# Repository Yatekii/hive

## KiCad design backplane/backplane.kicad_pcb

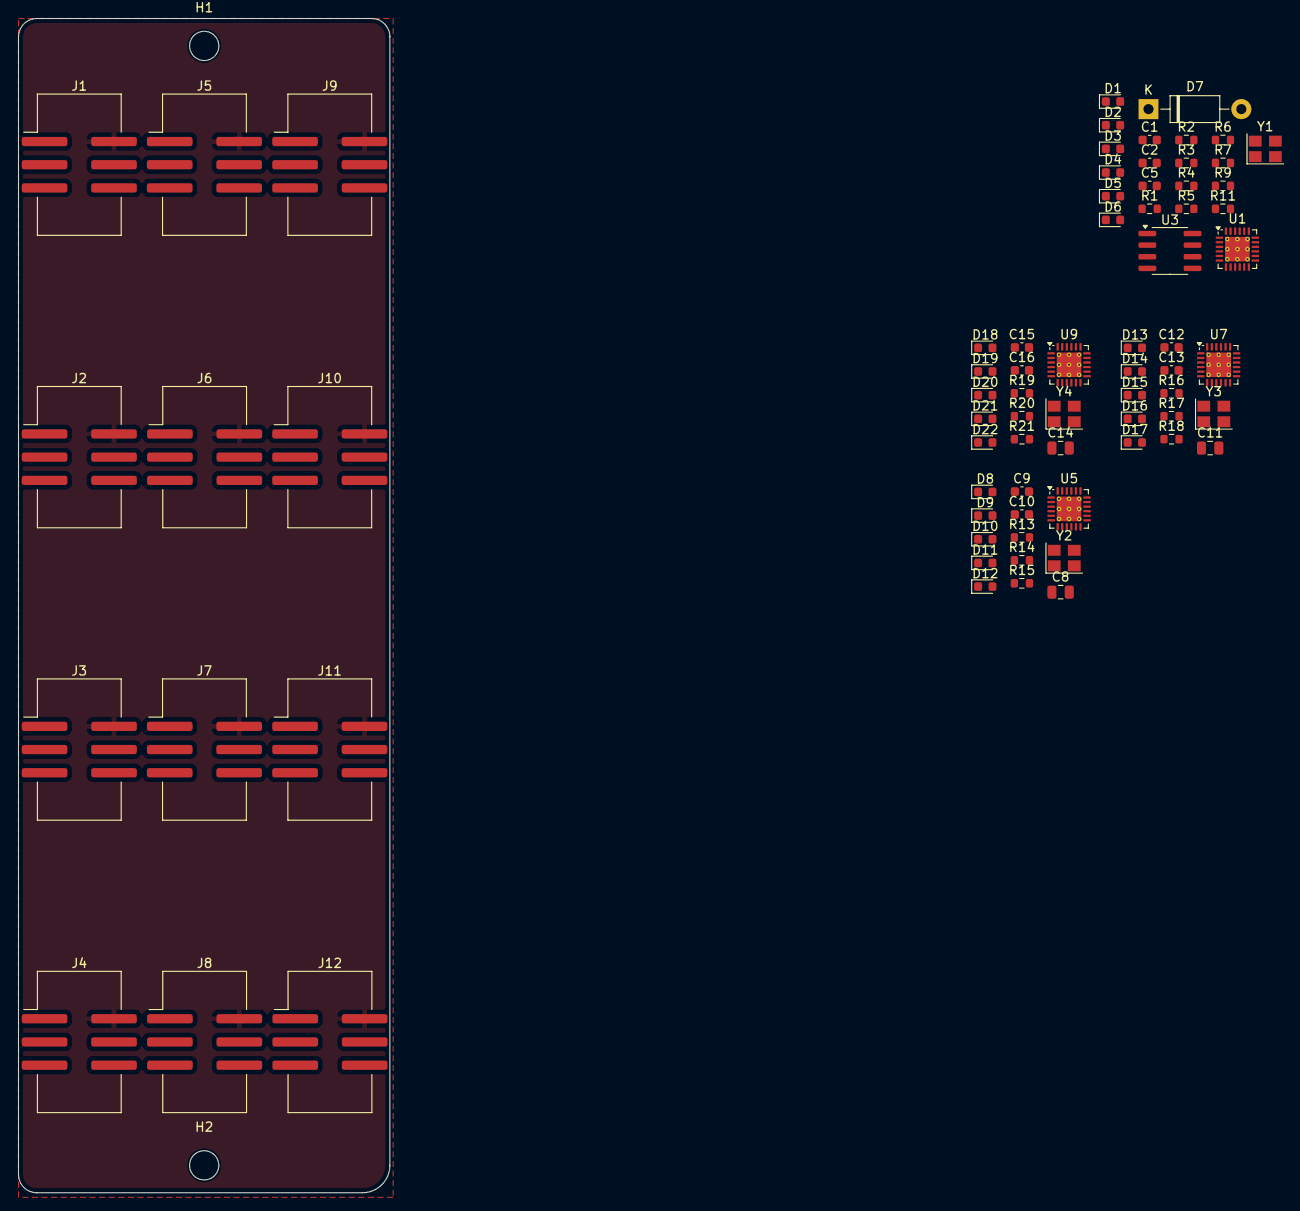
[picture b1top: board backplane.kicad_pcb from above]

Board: 2 copper layers, 40.6 x 128.5 mm, 75 parts (0 on the bottom side), 32 nets, no tracks yet.

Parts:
C1, C2, C5, C9, C10, C12, C13, C15, C16: 10u; C_0603_1608Metric
C8, C11, C14: 22uF; C_0805_2012Metric
D1, D2, D3, D4, D8, D9, D10, D11, D13, D14, D15, D16, D18, D19, D20, D21: GREEN; D_0603_1608Metric
D5, D12, D17, D22: RED; D_0603_1608Metric
D6: WHITE; D_0603_1608Metric
D7: 1N5819; D_DO-41_SOD81_P10.16mm_Horizontal
H1, H2: MountingHole; MountingHole_3.2mm_M3
J1, J2, J3, J4, J5, J6, J7, J8, J9, J10, J11, J12: Conn_02x03_Odd_Even; IDC-Header_2x03_P2.54mm_Vertical_SMD
R1, R2, R13, R14, R16, R17, R19, R20: 220; R_0603_1608Metric
R3, R15, R18, R21: 470; R_0603_1608Metric
R4, R5, R6, R7, R11: 10K; R_0603_1608Metric
R9: 1K; R_0603_1608Metric
U1, U5, U7, U9: QFN-24-1EP_4x4mm_P0.5mm_EP2.7x2.7mm_ThermalVias
U3: MC34063AD; SOIC-8_3.9x4.9mm_P1.27mm
Y1, Y2, Y3, Y4: Crystal_GND24; Crystal_SMD_3225-4Pin_3.2x2.5mm

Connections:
/+20v0: R4.1, R9.1, R11.1, U3.6 (Vin)
/PLED4_2: D1.2 (A), D2.1 (K), D3.2 (A), D4.1 (K), R3.2
/USB_3v3: C1.1, D5.2 (A), U1.20 (VDD33)
/USB_5v: C2.1, U1.19 (V5)
/XIN: U1.4 (XI), Y1.1
/XOUT: U1.3 (XO), Y1.3
/channel0/PLED4_2: D8.2 (A), D9.1 (K), D10.2 (A), D11.1 (K), R15.2
/channel0/USB_2_3v3: C9.1, D12.2 (A)
/channel0/USB_5v: C8.1, U5.19 (V5)
/channel1/PLED4_2: D13.2 (A), D14.1 (K), D15.2 (A), D16.1 (K), R18.2
/channel1/USB_2_3v3: C12.1, D17.2 (A)
/channel1/USB_5v: C11.1, U7.19 (V5)
/channel2/PLED4_2: D18.2 (A), D19.1 (K), D20.2 (A), D21.1 (K), R21.2
/channel2/USB_2_3v3: C15.1, D22.2 (A)
/channel2/USB_5v: C14.1, U9.19 (V5)
GND: C1.2, C2.2, C5.2, C8.2, C9.2, C10.2, C11.2, C12.2, C13.2, C14.2, C15.2, C16.2, D7.2 (A), J1.2, J2.2, J3.2, J4.2, J5.2, J6.2, J7.2, J8.2, J9.2, J10.2, J11.2, J12.2, R5.2, R7.2, U1.25 (GND), U3.4 (GND), U5.25 (GND), U7.25 (GND), U9.25 (GND), Y1.2, Y1.4, Y2.2, Y2.4, Y3.2, Y3.4, Y4.2, Y4.4
unnamed: D1.1 (K), D2.2 (A), R1.1
unnamed: D3.1 (K), D4.2 (A), R2.1
unnamed: D5.1 (K), R3.1
unnamed: D6.2 (A), R11.2
unnamed: D7.1 (K), U3.2 (SwE)
unnamed: D8.1 (K), D9.2 (A), R13.1
unnamed: D10.1 (K), D11.2 (A), R14.1
unnamed: D12.1 (K), R15.1
unnamed: D13.1 (K), D14.2 (A), R16.1
unnamed: D15.1 (K), D16.2 (A), R17.1
unnamed: D17.1 (K), R18.1
unnamed: D18.1 (K), D19.2 (A), R19.1
unnamed: D20.1 (K), D21.2 (A), R20.1
unnamed: D22.1 (K), R21.1
unnamed: U3.1 (SwC), U3.8 (DC)
VDD: C5.1, R6.2, R9.2

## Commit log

2025-04-19 Work on backplate schema
2025-04-20 Add 20V -> 3V3 buck
2025-04-22 More work on the backplane
